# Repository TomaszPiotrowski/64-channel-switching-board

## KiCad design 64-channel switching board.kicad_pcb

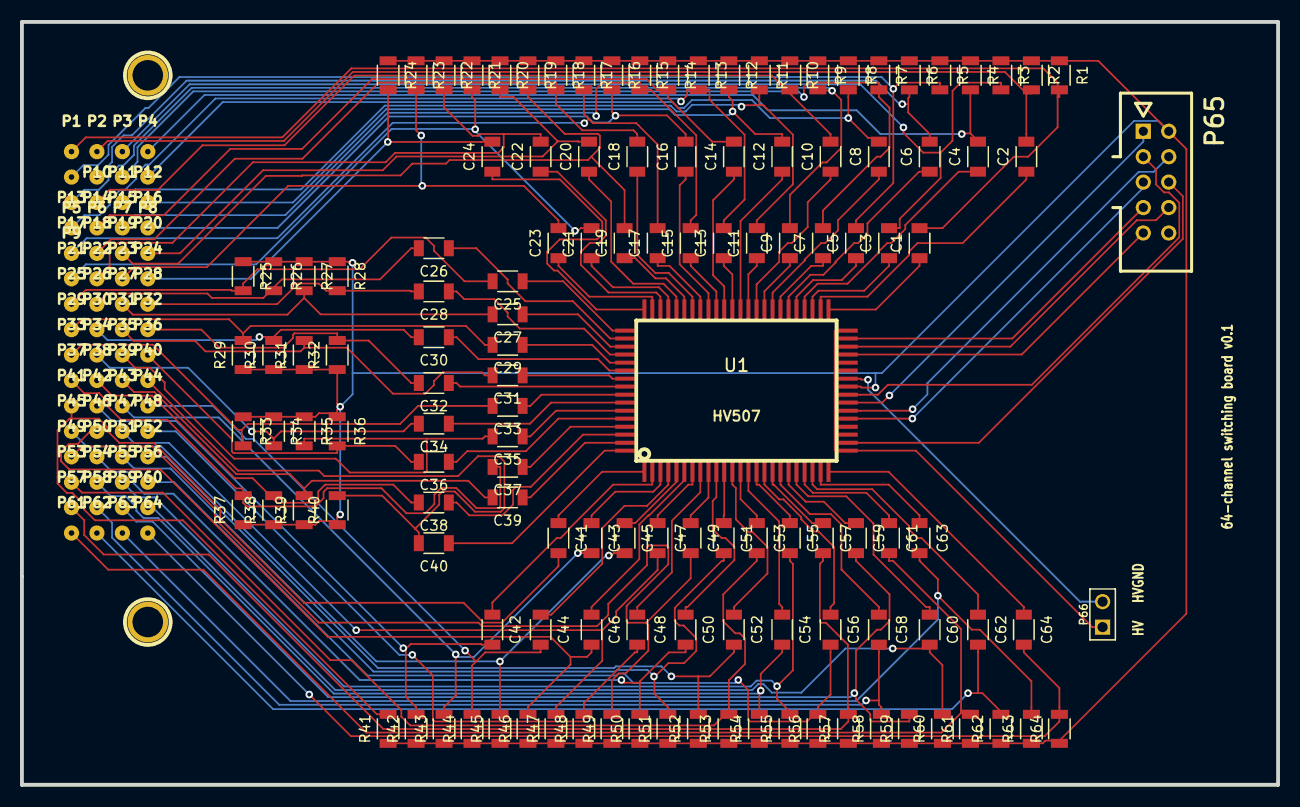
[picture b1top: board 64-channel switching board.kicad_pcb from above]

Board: 2 copper layers, 125.5 x 76.2 mm, 197 parts (0 on the bottom side), 139 nets.

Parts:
C1, C2, C3, C4, C5, C6, C7, C8, C9, C10, C11, C12, C13, C14, C15, C16, C17, C18, C19, C20, C21, C22, C23, C24, C25, C26, C27, C28, C29, C30, C31, C32, C33, C34, C35, C36, C37, C38, C39, C40, C41, C42, C43, C44, C45, C46, C47, C48, C49, C50, C51, C52, C53, C54, C55, C56, C57, C58, C59, C60, C61, C62, C63, C64: 3nF; C_1206
H2: H2; 1pin
H3: H3; 1pin
P1, P2, P3, P4, P5, P6, P7, P8, P9, P10, P11, P12, P13, P14, P15, P16, P17, P18, P19, P20, P21, P22, P23, P24, P25, P26, P27, P28, P29, P30, P31, P32, P33, P34, P35, P36, P37, P38, P39, P40, P41, P42, P43, P44, P45, P46, P47, P48, P49, P50, P51, P52, P53, P54, P55, P56, P57, P58, P59, P60, P61, P62, P63, P64: CONN_01X01; pogo_pin
P65: CONN_01X10; he10-10d
P66: CONN_01X02; PIN_ARRAY_2X1
R1, R2, R3, R4, R5, R6, R7, R8, R9, R10, R11, R12, R13, R14, R15, R16, R17, R18, R19, R20, R21, R22, R23, R24, R25, R26, R27, R28, R29, R30, R31, R32, R33, R34, R35, R36, R37, R38, R39, R40, R41, R42, R43, R44, R45, R46, R47, R48, R49, R50, R51, R52, R53, R54, R55, R56, R57, R58, R59, R60, R61, R62, R63, R64: 510k; R_1206
U1: HV507; PQFP80

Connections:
+5V: P65.1, U1.31
BL: P65.5, U1.29
CLK: P65.9, U1.37
DIOA: P65.6, U1.26
DIOB: P65.7, U1.39
DIR: P65.3, U1.32
GND: P65.2, R1.1, R2.1, R3.1, R4.1, R5.1, R6.1, R7.1, R8.1, R9.1, R10.1, R11.1, R12.1, R13.1, R14.1, R15.1, R16.1, R17.1, R18.1, R19.1, R20.1, R21.1, R22.1, R23.1, R24.1, R25.1, R26.1, R27.1, R28.1, R29.1, R30.1, R31.1, R32.1, R33.1, R34.1, R35.1, R36.1, R37.1, R38.1, R39.1, R40.1, R41.1, R42.1, R43.1, R44.1, R45.1, R46.1, R47.1, R48.1, R49.1, R50.1, R51.1, R52.1, R53.1, R54.1, R55.1, R56.1, R57.1, R58.1, R59.1, R60.1, R61.1, R62.1, R63.1, R64.1, U1.33
LE: P65.8, U1.38
unnamed: C1.1, U1.41
unnamed: C1.2, P1.1, R1.2
unnamed: C2.1, U1.42
unnamed: C2.2, P2.1, R2.2
unnamed: C3.1, U1.43
unnamed: C3.2, P3.1, R3.2
unnamed: C4.1, U1.44
unnamed: C4.2, P4.1, R4.2
unnamed: C5.1, U1.45
unnamed: C5.2, P5.1, R5.2
unnamed: C6.1, U1.46
unnamed: C6.2, P6.1, R6.2
unnamed: C7.1, U1.47
unnamed: C7.2, P7.1, R7.2
unnamed: C8.1, U1.48
unnamed: C8.2, P8.1, R8.2
unnamed: C9.1, U1.49
unnamed: C9.2, P9.1, R9.2
unnamed: C10.1, U1.50
unnamed: C10.2, P10.1, R10.2
unnamed: C11.1, U1.51
unnamed: C11.2, P11.1, R11.2
unnamed: C12.1, U1.52
unnamed: C12.2, P12.1, R12.2
unnamed: C13.1, U1.53
unnamed: C13.2, P13.1, R13.2
unnamed: C14.1, U1.54
unnamed: C14.2, P14.1, R14.2
unnamed: C15.1, U1.55
unnamed: C15.2, P15.1, R15.2
unnamed: C16.1, U1.56
unnamed: C16.2, P16.1, R16.2
unnamed: C17.1, U1.57
unnamed: C17.2, P17.1, R17.2
unnamed: C18.1, U1.58
unnamed: C18.2, P18.1, R18.2
unnamed: C19.1, U1.59
unnamed: C19.2, P19.1, R19.2
unnamed: C20.1, U1.60
unnamed: C20.2, P20.1, R20.2
unnamed: C21.1, U1.61
unnamed: C21.2, P21.1, R21.2
unnamed: C22.1, U1.62
unnamed: C22.2, P22.1, R22.2
unnamed: C23.1, U1.63
unnamed: C23.2, P23.1, R23.2
unnamed: C24.1, U1.64
unnamed: C24.2, P24.1, R24.2
unnamed: C25.1, U1.65
unnamed: C25.2, P25.1, R25.2
unnamed: C26.1, U1.66
unnamed: C26.2, P26.1, R26.2
unnamed: C27.1, U1.67
unnamed: C27.2, P27.1, R27.2
unnamed: C28.1, U1.68
unnamed: C28.2, P28.1, R28.2
unnamed: C29.1, U1.69
unnamed: C29.2, P29.1, R29.2
unnamed: C30.1, U1.70
unnamed: C30.2, P30.1, R30.2
unnamed: C31.1, U1.71
unnamed: C31.2, P31.1, R31.2
unnamed: C32.1, U1.72
unnamed: C32.2, P32.1, R32.2
unnamed: C33.1, U1.73
unnamed: C33.2, P33.1, R33.2
unnamed: C34.1, U1.74
unnamed: C34.2, P34.1, R34.2
unnamed: C35.1, U1.75
unnamed: C35.2, P35.1, R35.2
unnamed: C36.1, U1.76
unnamed: C36.2, P36.1, R36.2
unnamed: C37.1, U1.77
unnamed: C37.2, P37.1, R37.2
unnamed: C38.1, U1.78
unnamed: C38.2, P38.1, R38.2
unnamed: C39.1, U1.79
unnamed: C39.2, P39.1, R39.2
unnamed: C40.1, U1.80
unnamed: C40.2, P40.1, R40.2
unnamed: C41.1, U1.1
unnamed: C41.2, P41.1, R41.2
unnamed: C42.1, U1.2
unnamed: C42.2, P42.1, R42.2
unnamed: C43.1, U1.3
unnamed: C43.2, P43.1, R43.2
unnamed: C44.1, U1.4
unnamed: C44.2, P44.1, R44.2
unnamed: C45.1, U1.5
unnamed: C45.2, P45.1, R45.2
unnamed: C46.1, U1.6
unnamed: C46.2, P46.1, R46.2
unnamed: C47.1, U1.7
unnamed: C47.2, P47.1, R47.2
unnamed: C48.1, U1.8
unnamed: C48.2, P48.1, R48.2
unnamed: C49.1, U1.9
unnamed: C49.2, P49.1, R49.2
unnamed: C50.1, U1.10
unnamed: C50.2, P50.1, R50.2
unnamed: C51.1, U1.11
unnamed: C51.2, P51.1, R51.2
unnamed: C52.1, U1.12
unnamed: C52.2, P52.1, R52.2
unnamed: C53.1, U1.13
unnamed: C53.2, P53.1, R53.2
unnamed: C54.1, U1.14
unnamed: C54.2, P54.1, R54.2
unnamed: C55.1, U1.15
unnamed: C55.2, P55.1, R55.2
unnamed: C56.1, U1.16
unnamed: C56.2, P56.1, R56.2
unnamed: C57.1, U1.17
unnamed: C57.2, P57.1, R57.2
unnamed: C58.1, U1.18
unnamed: C58.2, P58.1, R58.2
unnamed: C59.1, U1.19
unnamed: C59.2, P59.1, R59.2
unnamed: C60.1, U1.20
unnamed: C60.2, P60.1, R60.2
unnamed: C61.1, U1.21
unnamed: C61.2, P61.1, R61.2
unnamed: C62.1, U1.22
unnamed: C62.2, P62.1, R62.2
unnamed: C63.1, U1.23
unnamed: C63.2, P63.1, R63.2
unnamed: C64.1, U1.24
unnamed: C64.2, P64.1, R64.2
unnamed: P66.1, U1.25, U1.40
unnamed: P66.2, U1.34
POL: P65.4, U1.30

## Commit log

2015-11-17 Updated schematic and pcb to have 64 resistors and capacitors. Also added a version with 40 pin connector
